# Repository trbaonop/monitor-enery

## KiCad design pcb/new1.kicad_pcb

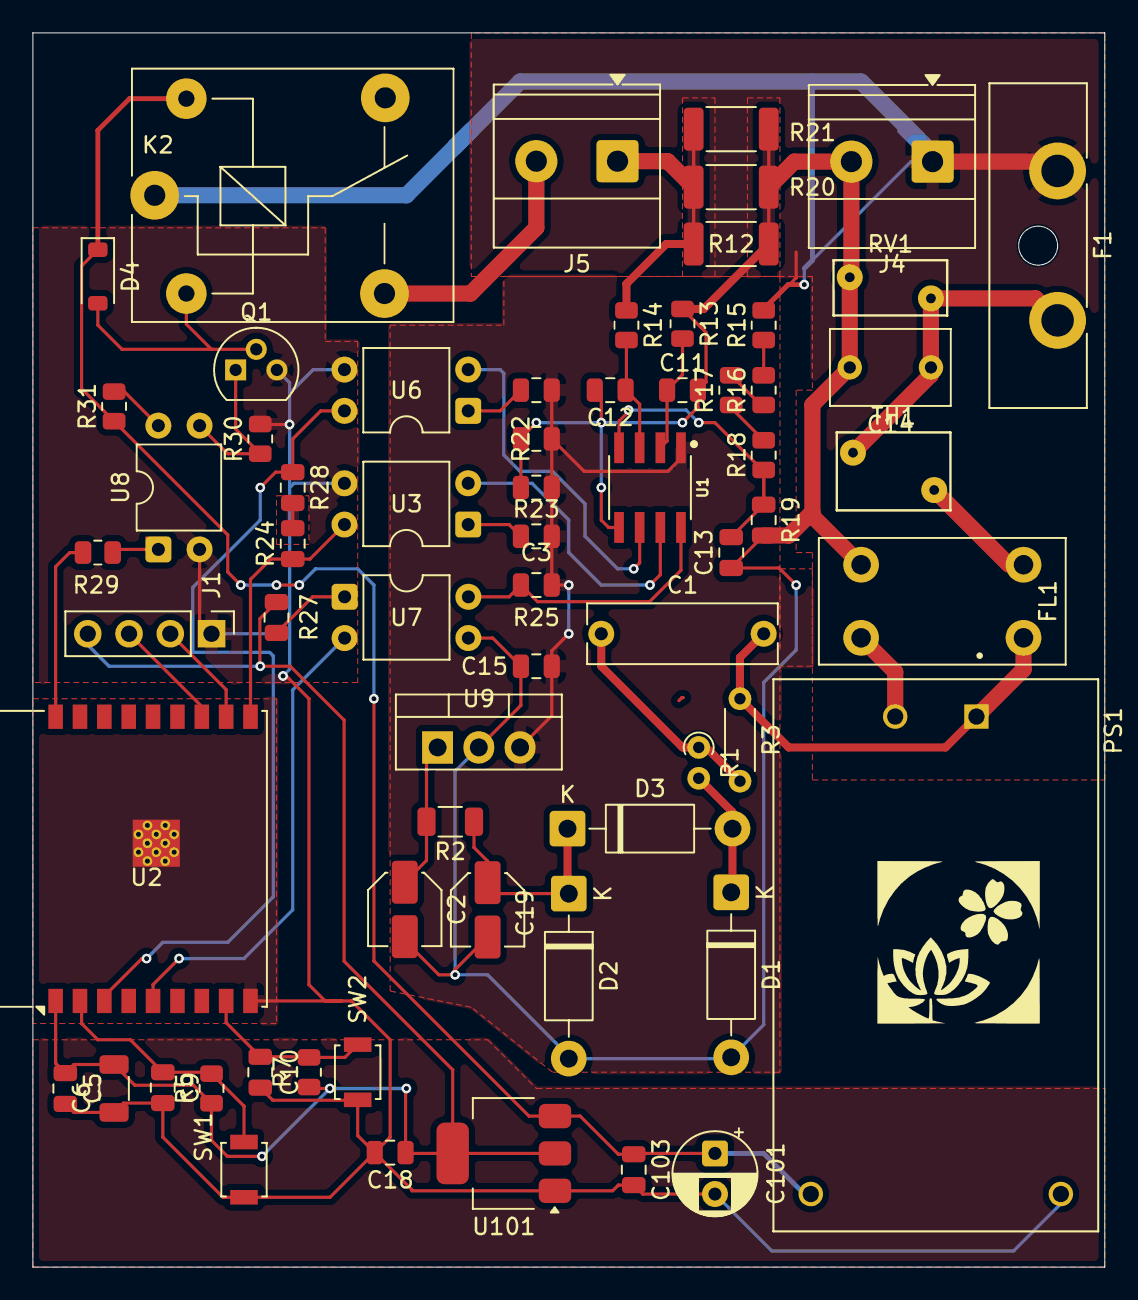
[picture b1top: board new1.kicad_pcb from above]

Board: 2 copper layers, 66.0 x 76.0 mm, 65 parts (0 on the bottom side), 41 nets.

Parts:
C1: C; C_Rect_L11.5mm_W3.5mm_P10.00mm_MKT
C2, C19: 470nF-25V; C_Elec_4x5.8
C3, C13: 100nF; C_0805_2012Metric
C4: 1uF; C_0805_2012Metric
C5: 4u7; C_0805_2012Metric
C6: 100n; C_1206_3216Metric
C9, C10: 100n; C_0805_2012Metric
C11, C12: 33nF; C_0805_2012Metric
C14: C; C_Rect_L7.2mm_W4.5mm_P5.00mm
C15, C18, C103: C; C_0805_2012Metric
C101: C_Polarized; CP_Radial_D5.0mm_P2.50mm
D1, D3: 1N4007; D_DO-41_SOD81_P10.16mm_Horizontal
D2: 1N47xxA; D_DO-41_SOD81_P10.16mm_Horizontal
D4: 1N4148W; D_SOD-123
F1: 500mA; Fuseholder_Blade_ATO_Littelfuse_Pudenz_2_Pin
FL1: Choke_CommonMode_PulseElectronics_PH9455x105NL; L_CommonMode_Wuerth_WE-CMB-XS
J1: Conn_01x04_Pin; PinHeader_1x04_P2.54mm_Vertical
J4, J5: Screw_Terminal_01x02; TerminalBlock_Phoenix_MKDS-1,5-2_1x02_P5.00mm_Horizontal
K2: SANYOU_SRD_Form_C; Relay_SPDT_SANYOU_SRD_Series_Form_C
PS1: HLK-PM01; CONV_HLK-PM01
Q1: Q_NPN; TO-92
R1: R; R_Axial_DIN0204_L3.6mm_D1.6mm_P1.90mm_Vertical
R2: 100R-0.5W; R_1206_3216Metric
R3: R; R_Axial_DIN0204_L3.6mm_D1.6mm_P5.08mm_Horizontal
R5, R7: 5k1; R_0805_2012Metric
R12, R20, R21: 0.004R-1%; R_2010_5025Metric
R13, R14: 1K; R_0805_2012Metric
R15, R16, R17, R18: 470K; R_0805_2012Metric
R19, R22, R23, R24, R25, R27, R28: 1K; C_0805_2012Metric
R29, R30, R31: 470; R_0805_2012Metric
RV1: Varistor; RV_Disc_D7mm_W3.4mm_P5mm
SW1, SW2: SW_SPST; SW_SPST_B3U-1000P
TH1: Thermistor_NTC; RV_Disc_D7mm_W4.8mm_P5mm
U1: HLW8032; SOIC127P600X144-8
U2: ESP32-C3-WROOM-02
U3, U6, U7, U8: PC817; DIP-4_W7.62mm
U9: LM78M05_TO220; TO-220-3_Vertical
U101: AMS1117-3.3; SOT-223-3_TabPin2

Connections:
+3.3V: C5.1, C6.1, C18.1, J1.4, R5.1, R7.1, R27.2, U2.1 (3V3), U101.2 (VO)
+5V: C101.1, C103.1, D4.1 (K), K2.5, PS1.4 (+VO), R31.1, U101.3 (VI)
+5V-1: C3.1, C4.1, C15.1, R22.2, R23.2, R25.2, U1.1 (VDD), U9.3 (VO)
+5V-2: R24.2, R28.2
/ACL: C1.2, FL1.2, PS1.1 (AC1), R3.1
/HVL: F1.1, J4.1, K2.1, R15.2
EN: C9.1, R5.2, SW1.2 (B), U2.2 (EN)
GND-1: C2.2, C3.2, C4.2, C11.2, C12.2, C13.1, C14.2, C15.2, C19.2, D1.2 (A), D2.2 (A), FL1.4, J4.2, R12.1, R13.1, R19.2, R20.1, R21.1, RV1.2, U1.5 (GND), U7.3, U9.2 (GND)
GND-2: C5.2, C6.2, C9.2, C10.2, C18.2, C101.2, C103.2, J1.1, PS1.3 (-VO), Q1.3, R30.2, SW1.1 (A), SW2.1 (A), U2.9 (GND), U2.19 (GND), U3.3, U6.3, U8.2, U101.1 (GND)
IO0: R29.2, U2.18 (IO0)
IO4: R28.1, U2.3 (IO4), U6.4
IO6: U2.5 (IO6), U7.2
IO9: C10.1, R7.2, SW2.2 (B), U2.8 (IO9)
unnamed: C1.1, R1.1, R3.2
unnamed: C14.1, F1.2, RV1.1, TH1.2
unnamed: D1.1 (K), D3.2 (A), R1.2
unnamed: C19.1, D2.1 (K), D3.1 (K), R2.1
unnamed: D4.2 (A), K2.2, Q1.2
unnamed: FL1.1, TH1.1
unnamed: J5.1, R12.2, R14.1, R20.2, R21.2
unnamed: J5.2, K2.3
unnamed: FL1.3, PS1.2 (AC2)
unnamed: Q1.1, R30.1, U8.3
unnamed: R15.1, R16.2
unnamed: R16.1, R17.2
unnamed: R17.1, R18.2
unnamed: R22.1, U6.1
unnamed: R23.1, U3.1
unnamed: R27.1, U7.1
unnamed: R29.1, U8.1
unnamed: R31.2, U8.4
unnamed: C12.1, R14.2, U1.3 (IN)
unnamed: C11.1, R13.2, U1.2 (IP)
unnamed: U1.7 (PF), U3.2
unnamed: R25.1, U1.8 (RX), U7.4
unnamed: U1.6 (TX), U6.2
unnamed: C13.2, R18.1, R19.1, U1.4 (VP)
unnamed: C2.1, R2.2, U9.1 (VI)
PF: R24.1, U2.10 (IO10), U3.4
RX: J1.2, U2.11 (IO20/RXD)
TX: J1.3, U2.12 (IO21/TXD)

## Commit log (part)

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2026-03-25 init
